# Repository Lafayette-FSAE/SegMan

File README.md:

# SegMan
A KiCad Schematic for SegMan, A Segment Management Board for the Lafayette FSAE Accumulator Management System

---

## SegMan is Dead, Long live PacMan

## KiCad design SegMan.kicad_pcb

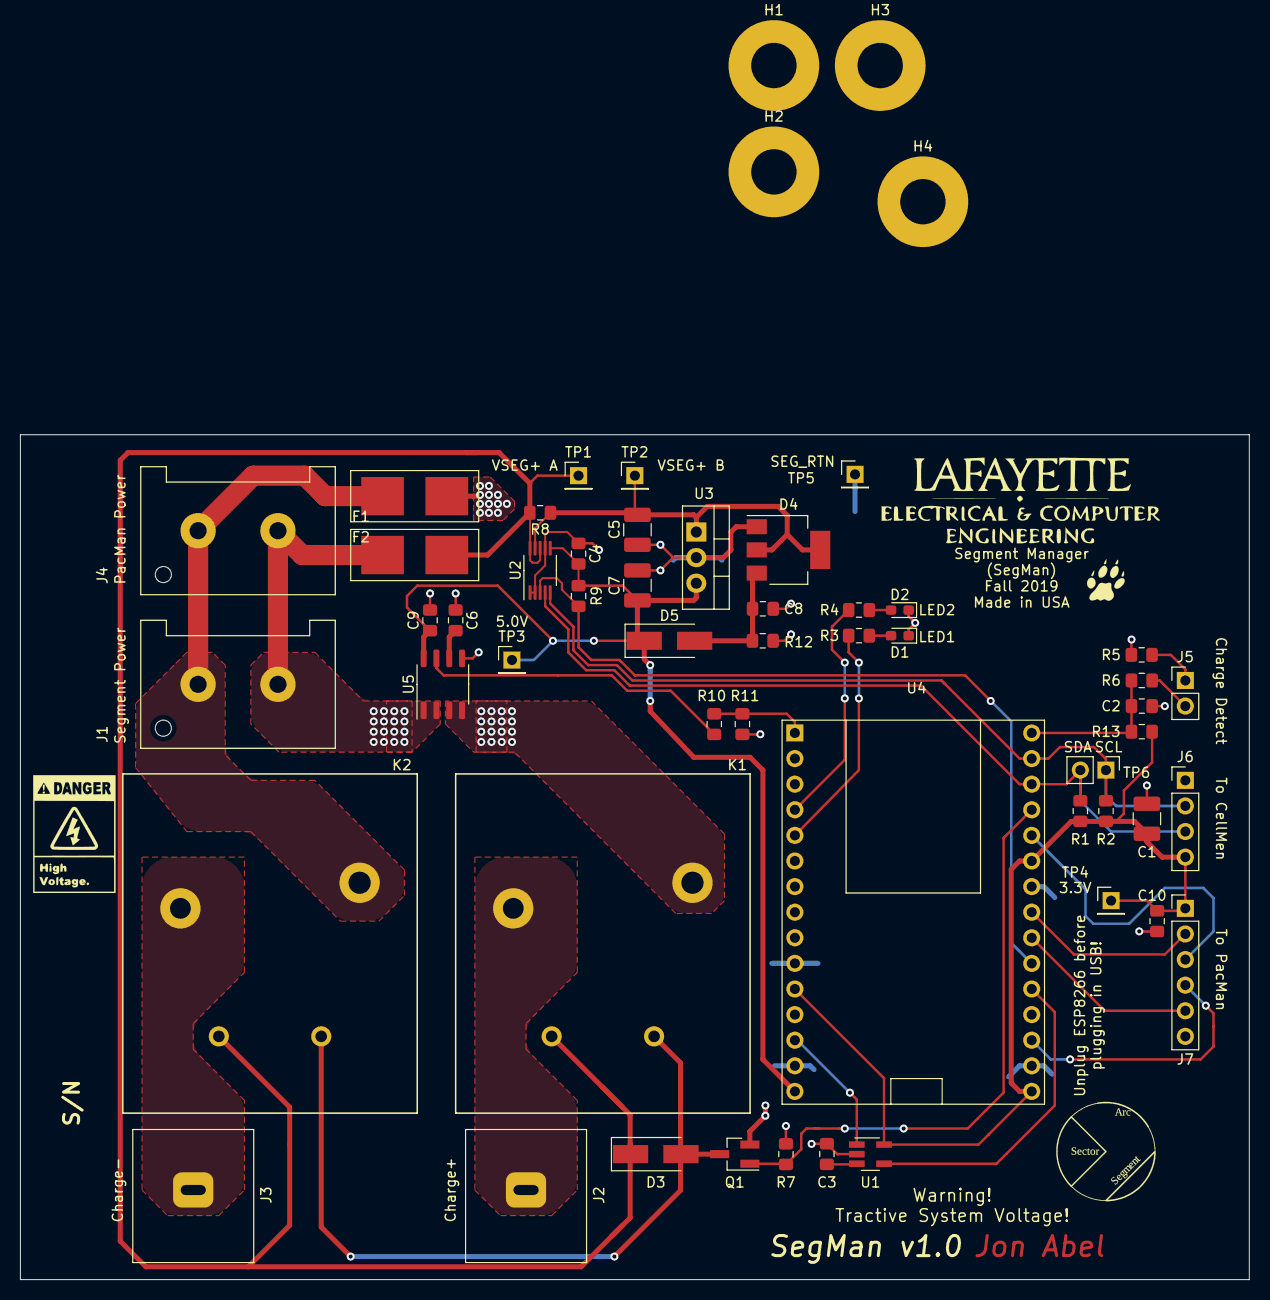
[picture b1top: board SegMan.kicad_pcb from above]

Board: 2 copper layers, 121.9 x 83.8 mm, 55 parts (0 on the bottom side), 34 nets.

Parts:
C1, C5: 10u; C_1210_3225Metric_Pad1.42x2.65mm_HandSolder
C2, C3, C4, C10: 0.1u; C_0805_2012Metric_Pad1.15x1.40mm_HandSolder
C6: 1n; C_0805_2012Metric_Pad1.15x1.40mm_HandSolder
C7: 22u; C_1210_3225Metric_Pad1.42x2.65mm_HandSolder
C8: C; C_0805_2012Metric_Pad1.15x1.40mm_HandSolder
C9: 1u; C_0805_2012Metric_Pad1.15x1.40mm_HandSolder
D1: LED1; LED_0603_1608Metric_Pad1.05x0.95mm_HandSolder
D2: LED2; LED_0603_1608Metric_Pad1.05x0.95mm_HandSolder
D3: S1B; D_SMA_Handsoldering
D4: X0202MN 5BA4; SOT-223
D5: SMAZ5V6; D_SMA_Handsoldering
F1, F2: 250mA; 0154.500DRL
H1, H2, H3, H4: MountingHole_Pad; MountingHole_4.5mm_Pad
J1: SegPower; DF22-2P-7.92
J2: CHRG+; DF22-1P-7.92
J3: CHRG-; DF22-1P-7.92
J4: PacPower; DF22-2P-7.92
J5: ChrgDetect; PinHeader_1x02_P2.54mm_Vertical
J6: I2CSeg; PinHeader_1x04_P2.54mm_Vertical
J7: I2CPac; PinHeader_1x06_P2.54mm_Vertical
K1, K2: T9AS1D12-24; T9AS1D12
Q1: BSS138W; SOT-23_Handsoldering
R1, R2, R5, R6: 5k; R_0805_2012Metric_Pad1.15x1.40mm_HandSolder
R3, R4: 270; R_0805_2012Metric_Pad1.15x1.40mm_HandSolder
R7: 100k; R_0805_2012Metric_Pad1.15x1.40mm_HandSolder
R8: 0.5; R_0805_2012Metric_Pad1.15x1.40mm_HandSolder
R9, R10: 10k; R_0805_2012Metric_Pad1.15x1.40mm_HandSolder
R11: 22k; R_0805_2012Metric_Pad1.15x1.40mm_HandSolder
R12: R; R_0805_2012Metric_Pad1.15x1.40mm_HandSolder
R13: 500k; R_0805_2012Metric_Pad1.15x1.40mm_HandSolder
TP1, TP2, TP3, TP4, TP5: TestPoint; PinHeader_1x01_P2.54mm_Vertical
TP6: TestPoint_2Pole; PinHeader_1x02_P2.54mm_Vertical
U1: ADM6320; SOT-23-5_HandSoldering
U2: INA226; VSSOP-10_3x3mm_P0.5mm
U3: V7805-500; TO-220-3_Vertical
U4: ESP8266NodeMCUDevKit; NodeMCUESP8266
U5: ACHS-7122; SO-8_3.9x4.9mm_P1.27mm

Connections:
/CHRG+: J2.1, K1.3
/CHRG-: J3.1, K2.3
/CHRG_DET: C2.2, R6.1, R13.2, U4.30
/CURRENTSENSE: R10.2, U5.7
/CurrentSensor+: K1.4, U5.3, U5.4
/EN_CHRG: Q1.1, R7.1, U4.27
/GLV_GND: H1.1, H2.1, H3.1, H4.1
/LED1: R3.2, U4.5
/LED2: R4.2, U4.4
/MISC_FROM_PAC: J7.4, U4.18
/MISC_TO_PAC: J7.3, U4.26
/SCL_PAC: J7.5, U4.22
/SCL_SEG: J6.2, R2.2, TP6.1, U2.5, U4.29
/SDA_PAC: J7.2, U4.23
/SDA_SEG: J6.3, R1.2, TP6.2, U2.4, U4.28
/SEG_3V3: C1.2, C10.2, J6.4, J7.1, R1.1, R2.1, R13.1, TP4.1, U1.5, U4.11, U4.16, U4.25
/SEG_5V: C4.2, C7.1, C9.1, D5.1, R9.2, TP3.1, U2.6, U3.3, U4.15, U5.8
/SEG_RTN: C1.1, C2.1, C3.2, C4.1, C5.2, C6.1, C7.2, C8.2, C9.2, C10.1, D1.1, D2.1, D4.1, F2.2, J6.1, J7.6, Q1.2, R5.1, R7.2, R11.1, R12.2, TP5.1, U1.2, U2.1, U2.2, U2.7, U3.2, U4.10, U4.14, U4.17, U4.24, U5.5
/VSEG+: F1.1, J1.1, J4.1, U5.1, U5.2
/VSEG-: F2.1, J1.2, J4.2, K2.4
/VSEG_FUSE_A: D3.1, F1.2, K1.1, K2.1, R8.2, TP1.1, U2.8, U2.10
/VSEG_FUSE_B: C5.1, D4.2, D4.4, R8.1, TP2.1, U2.9, U3.1
/WATCHDOG: U1.4, U4.20
/~ALERT: R9.1, U2.3, U4.21
/~RESET_ESP: U1.1, U4.13
unnamed: C3.1, U1.3
unnamed: C6.2, U5.6
unnamed: C8.1, D4.3, D5.2, R12.1
unnamed: D1.2, R3.1
unnamed: D2.2, R4.1
unnamed: D3.2, K1.2, K2.2, Q1.3
unnamed: J5.1, R5.2
unnamed: J5.2, R6.2
unnamed: R10.1, R11.2, U4.1

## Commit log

2019-09-25 Pushing current progress
2019-09-26 Quick note change
2019-10-02 More work
2019-10-07 More work, what's new
2019-10-07 I'm not telling
2019-10-08 go ahead and guess
2019-10-08 v1.0
2019-10-08 Wouldn't you like to know, weatherboy?
2019-10-08 Added some resistor footprint associations... or did I?
2019-10-11 What if we kissed in the lab? Haha just kidding... ..unless?
2019-10-16 v1.0 of the PCB is done, oh, word?
2019-10-16 quick update before I retreat from the cave
2019-10-17 the rise of ChordMan
2019-10-23 Board v1 complete, I think
2019-10-28 Lots of changes, no working version, somewhere in between 1.2 and 1.3
2019-10-29 schematic 1.3 pretty much ready for review
